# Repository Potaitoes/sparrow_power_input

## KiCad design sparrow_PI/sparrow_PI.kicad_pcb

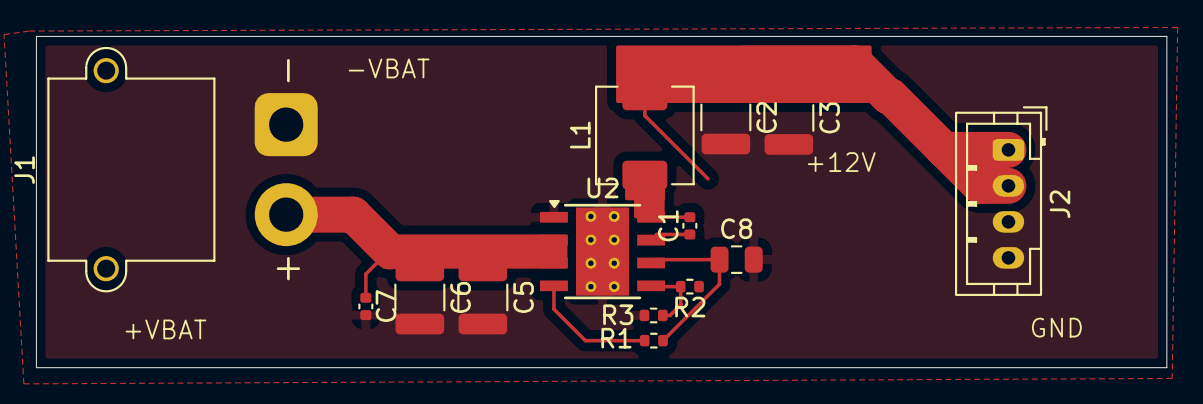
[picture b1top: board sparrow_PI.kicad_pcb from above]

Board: 2 copper layers, 62.8 x 18.4 mm, 14 parts (0 on the bottom side), 8 nets.

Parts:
C1: 0.1u/x7r/50V/ceramic; C_0402_1005Metric
C2, C3, C5, C6: 10u/XR7/50V/Ceramic; C_1210_3225Metric
C7: 220n/XR7/50V/Ceramic; C_0402_1005Metric
C8: 1u/X7R/16V; C_0805_2012Metric
J1: Conn_01x02_Pin; AMASS_XT30PW-M_1x02_P2.50mm_Horizontal
J2: Conn_01x02_Pin; JST_PH_B4B-PH-K_1x04_P2.00mm_Vertical
L1: 3.3uH/4.5AIsat/3VIrms; L_KOHERelec_MDA5030
R1: 100k; R_0402_1005Metric
R2: 110k; R_0402_1005Metric
R3: 10k; R_0402_1005Metric
U2: LMR33640DDDA; Texas_HSOP-8-1EP_3.9x4.9mm_P1.27mm_ThermalVias

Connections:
+12V: C2.1, C3.1, J2.1, J2.2, L1.2, R2.1
+BATT: C5.1, C6.1, C7.1, J1.2, U2.2 (VIN), U2.3 (EN)
/FB: R2.2, R3.1, U2.5 (FB)
/PG: R1.1, U2.4 (PG)
GND: C2.2, C3.2, C5.2, C6.2, C7.2, C8.2, J1.1, J2.3, J2.4, R3.2, U2.1 (GND), U2.9 (GND)
unnamed: C1.1, U2.7 (BOOT)
unnamed: C1.2, L1.1, U2.8 (SW)
unnamed: C8.1, R1.2, U2.6 (VCC)

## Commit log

2026-06-10 designed, routed, ready for review and ship
